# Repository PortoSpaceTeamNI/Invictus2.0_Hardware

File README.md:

Este repositório é usado para gerir as versões dos projetos KiCAD do sistema de Avionics da Porto Space Team.
Está dividido em 2 secções: 
  1. A biblioteca de símbolos, footprints e modelos 3D dos diversos componentes usados no design, cada pasta do símbolo deve apenas incluir os ficheiros de .kicad_sym, .kicad_mod e .step todos juntos apenas dentro de uma única pasta com um nome adequado.
  2. A pasta Boards que contém os diversos ficheiros de schematic (.kicad_sch), pcb (.kicad_pcb) e project (.kicad_pro) de todo o sistema de Avionics.

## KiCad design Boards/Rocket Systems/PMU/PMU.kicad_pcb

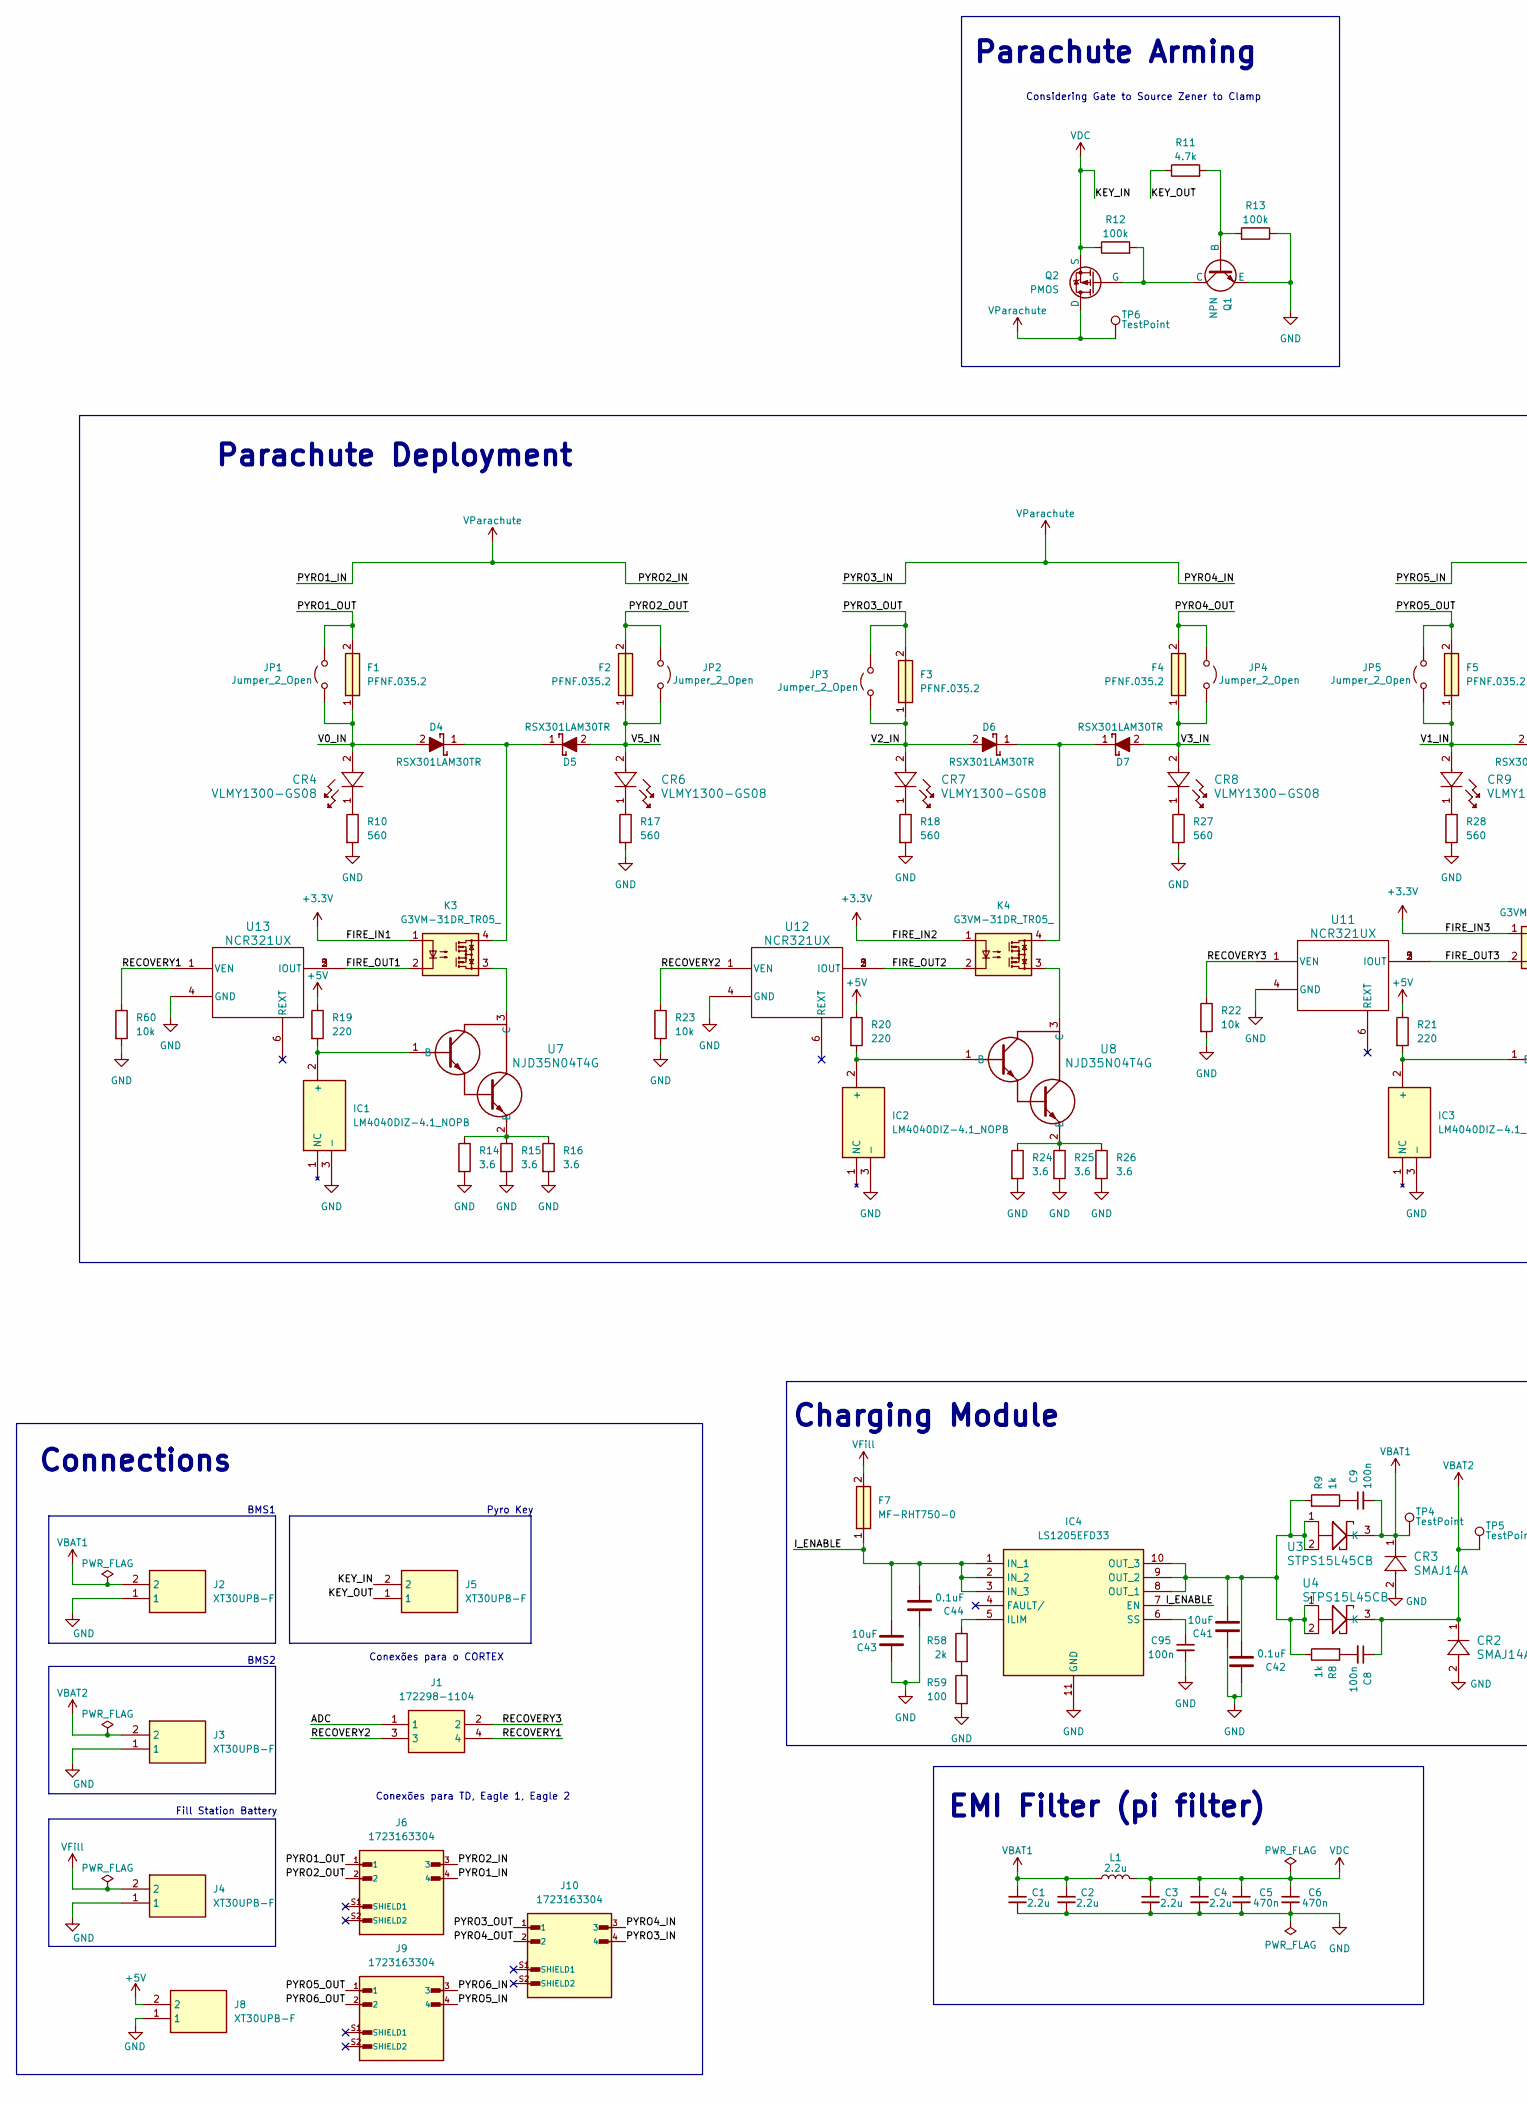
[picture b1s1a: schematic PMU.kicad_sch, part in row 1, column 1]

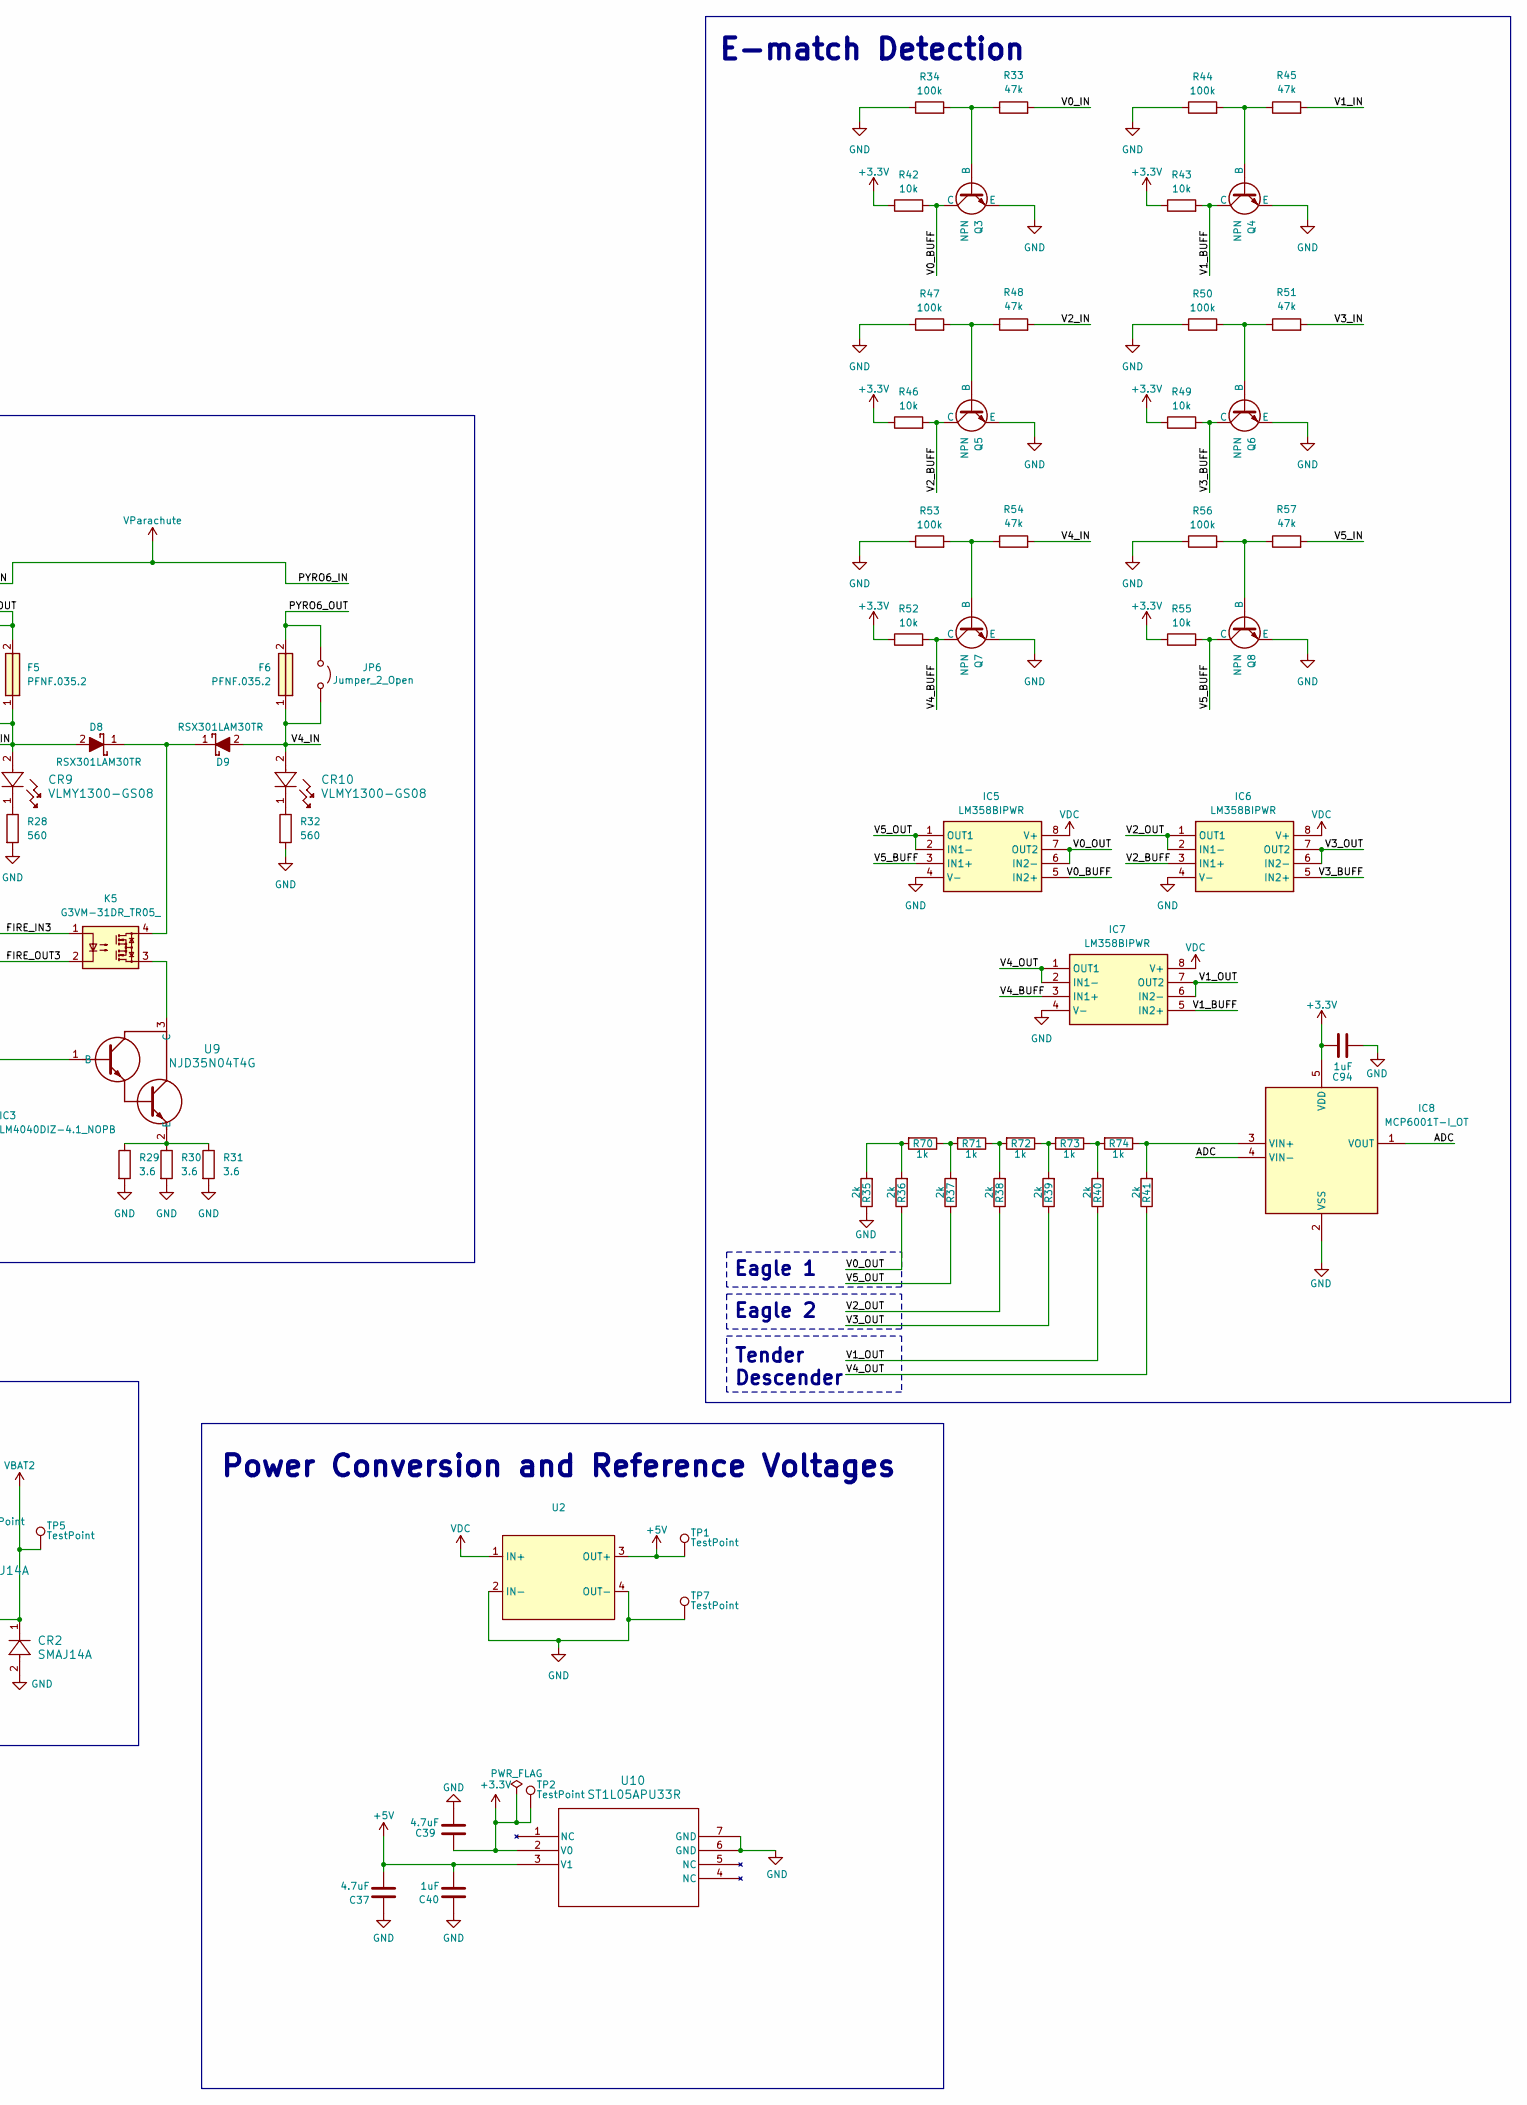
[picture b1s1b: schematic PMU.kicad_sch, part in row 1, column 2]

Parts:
C1, C2, C3, C4: 2.2u; Capacitor_1206
C5, C6: 470n; Capacitor_1206
C8, C9: 100n; Capacitor_0603
C37, C39: 4.7uF; Capacitor_0402
C40, C94: 1uF; Capacitor_0402
C41, C43: 10uF; Capacitor_0402
C42, C44: 0.1uF; Capacitor_0402
C95: 100n; Capacitor_0402
CR2, CR3: SMAJ14A; SMASeries_LTF
CR4, CR6, CR7, CR8, CR9, CR10: VLMY1300-GS08; LEDC1608X100N
D4, D5, D6, D7, D8, D9: RSX301LAM30TR; DIOM5026X220N; Mouser Part Number 755-RSX301L-30DDTE25
F1, F2, F3, F4, F5, F6: PFNF.035.2; FUS1206_24N_SCH; Mouser Part Number 693-PFNF.035.2
F7: MF-RHT750-0; MFRHT7500; Mouser Part Number 693-PFNF.035.2
IC1, IC2, IC3: LM4040DIZ-4.1_NOPB; LM336BLPE325; Mouser Part Number 926-LM4040DIZ41NOPB
IC4: LS1205EFD33; SON50P300X300X80-11N; Mouser Part Number 576-LS1205EFD33
IC5, IC6, IC7: LM358BIPWR; SOP65P640X120-8N; Mouser Part Number 595-LM358BIPWR
IC8: MCP6001T-I_OT; SOT95P270X145-5N; Mouser Part Number 579-MCP6001T-I/OT
J1: 172298-1104; 172298-YY04; Mouser Part Number 538-172298-1104
J2, J3, J4, J5, J8: XT30UPB-F; XT30UPBF; Manufacturer_Part_Number XT30UPB-F
J6, J9, J10: 1723163304; MOLEX_1723163304; PARTREV D
JP1, JP2, JP3, JP4, JP5, JP6: Jumper_2_Open; SolderJumper-2_P1.3mm_Open_RoundedPad1.0x1.5mm
K3, K4, K5: G3VM-31DR_TR05_; G3VM31DRTR05; Mouser Part Number 653-G3VM-31DR(TR05)
L1: 2.2u; SPM10065VT-2R2M-D
Q1, Q3, Q4, Q5, Q6, Q7, Q8: NPN; SOT95P230X110-3N
Q2: PMOS; IPD380P06NMATMA1
R8, R9: 1k; RES_0805
R10, R17, R18, R27, R28, R32: 560; RES_0805
R11: 4.7k; RES_0805
R12, R13: 100k; RES_0805
R14, R15, R16, R24, R25, R26, R29, R30, R31: 3.6; RESC3263X80N
R19, R20, R21: 220; RES_0805
R22, R23, R60: 10k; RES_0402
R33, R45, R48, R51, R54, R57: 47k; RES_0603
R34, R44, R47, R50, R53, R56: 100k; RES_0603
R35, R36, R37, R38, R39, R40, R41, R58: 2k; RES_0603
R42, R43, R46, R49, R52, R55: 10k; RES_0603
R59: 100; RES_0603
R70, R71, R72, R73, R74: 1k; RES_0603
TP1, TP2, TP4, TP5, TP6, TP7: TestPoint; TestPoint_Pad_2.0x2.0mm
U2: DCDC_Module
U3, U4: STPS15L45CB; DPAK_STM
U7, U8, U9: NJD35N04T4G; DPAK-4_6P22X6P73_ONS
U10: ST1L05APU33R; DFN_5APU33R_STM
U11, U12, U13: NCR321UX; TSOP6_SOT457_NEX

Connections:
+3.3V: C39.2, C94.1, IC8.5 (VDD), K3.1, K4.1, K5.1, R42.1, R43.1, R46.1, R49.1, R52.1, R55.1, TP2.1, U10.2 (V0)
+5V: C37.2, C40.2, J8.2, R19.1, R20.1, R21.1, TP1.1, U2.3 (OUT+), U10.3 (V1)
/ADC: IC8.1 (VOUT), IC8.4 (VIN-), J1.1
/FIRE_OUT1: K3.2, U13.2 (IOUT), U13.3 (IOUT), U13.5 (IOUT)
/FIRE_OUT2: K4.2, U12.2 (IOUT), U12.3 (IOUT), U12.5 (IOUT)
/FIRE_OUT3: K5.2, U11.2 (IOUT), U11.3 (IOUT), U11.5 (IOUT)
/I_ENABLE: C43.2, C44.2, F7.1, IC4.1 (IN_1), IC4.2 (IN_2), IC4.3 (IN_3), IC4.7 (EN)
/KEY_OUT: J5.1, R11.1
/PYRO1_OUT: F1.2, J6.1, JP1.2 (B)
/PYRO2_OUT: F2.2, J6.2, JP2.2 (B)
/PYRO3_OUT: F3.2, J10.1, JP3.2 (B)
/PYRO4_OUT: F4.2, J10.2, JP4.2 (B)
/PYRO5_OUT: F5.2, J9.1, JP5.2 (B)
/PYRO6_OUT: F6.2, J9.2, JP6.2 (B)
/RECOVERY1: J1.4, R60.1, U13.1 (VEN)
/RECOVERY2: J1.3, R23.1, U12.1 (VEN)
/RECOVERY3: J1.2, R22.1, U11.1 (VEN)
/V0_BUFF: IC5.5 (IN2+), Q3.1 (C), R42.2
/V0_IN: CR4.2, D4.2 (A), F1.1, JP1.1 (A), R33.2
/V0_OUT: IC5.6 (IN2-), IC5.7 (OUT2), R36.1
/V1_BUFF: IC7.5 (IN2+), Q4.1 (C), R43.2
/V1_IN: CR9.2, D8.2 (A), F5.1, JP5.1 (A), R45.2
/V1_OUT: IC7.6 (IN2-), IC7.7 (OUT2), R40.1
/V2_BUFF: IC6.3 (IN1+), Q5.1 (C), R46.2
/V2_IN: CR7.2, D6.2 (A), F3.1, JP3.1 (A), R48.2
/V2_OUT: IC6.1 (OUT1), IC6.2 (IN1-), R38.1
/V3_BUFF: IC6.5 (IN2+), Q6.1 (C), R49.2
/V3_IN: CR8.2, D7.2 (A), F4.1, JP4.1 (A), R51.2
/V3_OUT: IC6.6 (IN2-), IC6.7 (OUT2), R39.1
/V4_BUFF: IC7.3 (IN1+), Q7.1 (C), R52.2
/V4_IN: CR10.2, D9.2 (A), F6.1, JP6.1 (A), R54.2
/V4_OUT: IC7.1 (OUT1), IC7.2 (IN1-), R41.1
/V5_BUFF: IC5.3 (IN1+), Q8.1 (C), R55.2
/V5_IN: CR6.2, D5.2 (A), F2.1, JP2.1 (A), R57.2
/V5_OUT: IC5.1 (OUT1), IC5.2 (IN1-), R37.1
GND: C1.2, C2.2, C3.2, C4.2, C5.2, C6.2, C37.1, C39.1, C40.1, C41.1, C42.1, C43.1, C44.1, C94.2, C95.2, CR2.2, CR3.2, IC1.3 (-), IC2.3 (-), IC3.3 (-), IC4.11 (GND), IC5.4 (V-), IC6.4 (V-), IC7.4 (V-), IC8.2 (VSS), J2.1, J3.1, J4.1, J8.1, Q1.3 (E), Q3.3 (E), Q4.3 (E), Q5.3 (E), Q6.3 (E), Q7.3 (E), Q8.3 (E), R10.2, R13.1, R14.2, R15.2, R16.2, R17.2, R18.2, R22.2, R23.2, R24.2, R25.2, R26.2, R27.2, R28.2, R29.2, R30.2, R31.2, R32.2, R34.1, R35.1, R44.1, R47.1, R50.1, R53.1, R56.1, R59.2, R60.2, TP7.1, U2.2 (IN-), U2.4 (OUT-), U10.6 (GND), U10.7 (GND), U11.4 (GND), U12.4 (GND), U13.4 (GND)
unnamed: C8.2, R8.2
unnamed: C9.1, R9.1
unnamed: CR4.1, R10.1
unnamed: CR6.1, R17.1
unnamed: CR7.1, R18.1
unnamed: CR8.1, R27.1
unnamed: CR9.1, R28.1
unnamed: CR10.1, R32.1
unnamed: D4.1 (K), D5.1 (K), K3.4
unnamed: D6.1 (K), D7.1 (K), K4.4
unnamed: D8.1 (K), D9.1 (K), K5.4
unnamed: IC1.2 (+), R19.2, U7.1 (B)
unnamed: IC2.2 (+), R20.2, U8.1 (B)
unnamed: IC3.2 (+), R21.2, U9.1 (B)
unnamed: IC4.5 (ILIM), R58.1
unnamed: C41.2, C42.2, IC4.8 (OUT_1), IC4.9 (OUT_2), IC4.10 (OUT_3), R8.1, R9.2, U3.1, U3.2, U4.1, U4.2
unnamed: C95.1, IC4.6 (SS)
unnamed: IC8.3 (VIN+), R41.2, R74.1
unnamed: Q1.2 (B), R11.2, R13.2
unnamed: Q1.1 (C), Q2.2 (G), R12.2
unnamed: Q3.2 (B), R33.1, R34.2
unnamed: Q4.2 (B), R44.2, R45.1
unnamed: Q5.2 (B), R47.2, R48.1
unnamed: Q6.2 (B), R50.2, R51.1
unnamed: Q7.2 (B), R53.2, R54.1
unnamed: Q8.2 (B), R56.2, R57.1
unnamed: R35.2, R36.2, R70.2
unnamed: R37.2, R70.1, R71.2
unnamed: R38.2, R71.1, R72.2
unnamed: R39.2, R72.1, R73.2
unnamed: R40.2, R73.1, R74.2
unnamed: R58.2, R59.1
unnamed: K3.3, U7.3 (C)
unnamed: R14.1, R15.1, R16.1, U7.2 (E)
unnamed: K4.3, U8.3 (C)
unnamed: R24.1, R25.1, R26.1, U8.2 (E)
unnamed: K5.3, U9.3 (C)
unnamed: R29.1, R30.1, R31.1, U9.2 (E)
VBAT1: C1.1, C2.1, C9.2, CR3.1, J2.2, L1.1, TP4.1, U3.3 (K)
VBAT2: C8.1, CR2.1, J3.2, TP5.1, U4.3 (K)
VDC: C3.1, C4.1, C5.1, C6.1, IC5.8 (V+), IC6.8 (V+), IC7.8 (V+), J5.2, L1.2, Q2.3 (S), R12.1, U2.1 (IN+)
VFill: F7.2, J4.2
VParachute: J6.3, J6.4, J9.3, J9.4, J10.3, J10.4, Q2.1 (D), TP6.1

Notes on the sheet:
Pyro Key
BMS1
Conexões para o CORTEX
Parachute Arming
E-match Detection
Connections
Power Conversion and Reference Voltages
Considering Gate to Source Zener to Clamp
BMS2
Charging Module
Fill Station Battery
Conexões para TD, Eagle 1, Eagle 2
Parachute Deployment
Eagle 2
EMI Filter (pi filter)
Eagle 1
Tender Descender

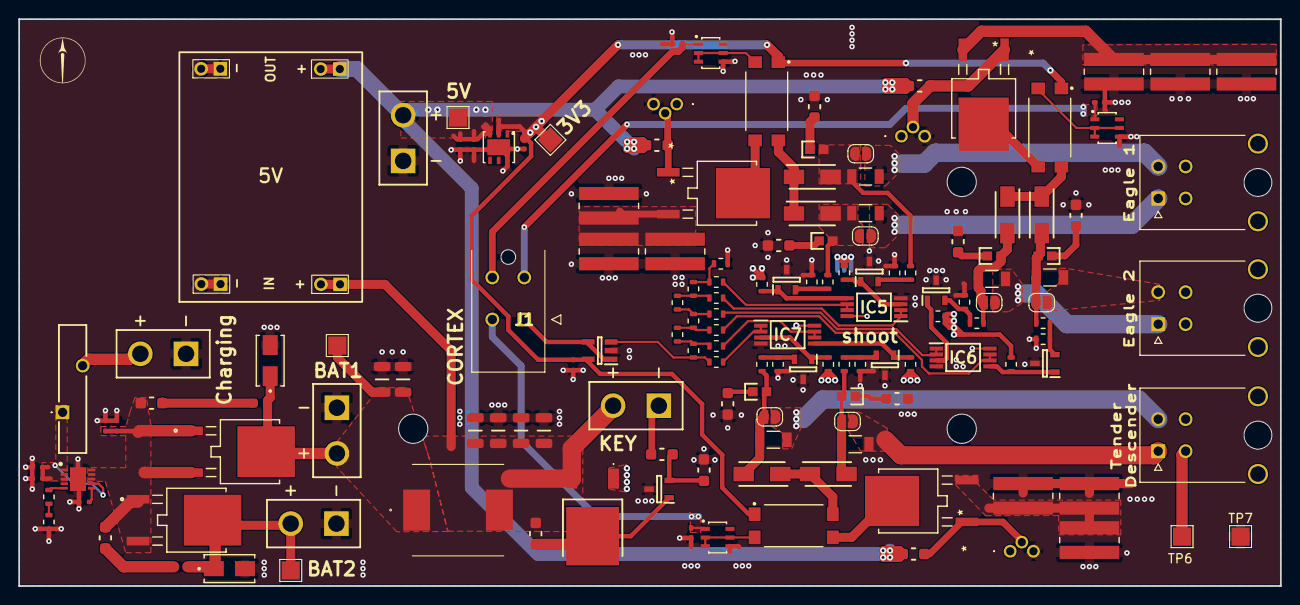
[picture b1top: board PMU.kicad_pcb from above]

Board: 4 copper layers, 138.0 x 62.0 mm, 150 parts (0 on the bottom side), 79 nets.

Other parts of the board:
H1, H2, H3: MountingHole; MountingHole_3.2mm_M3_ISO7380

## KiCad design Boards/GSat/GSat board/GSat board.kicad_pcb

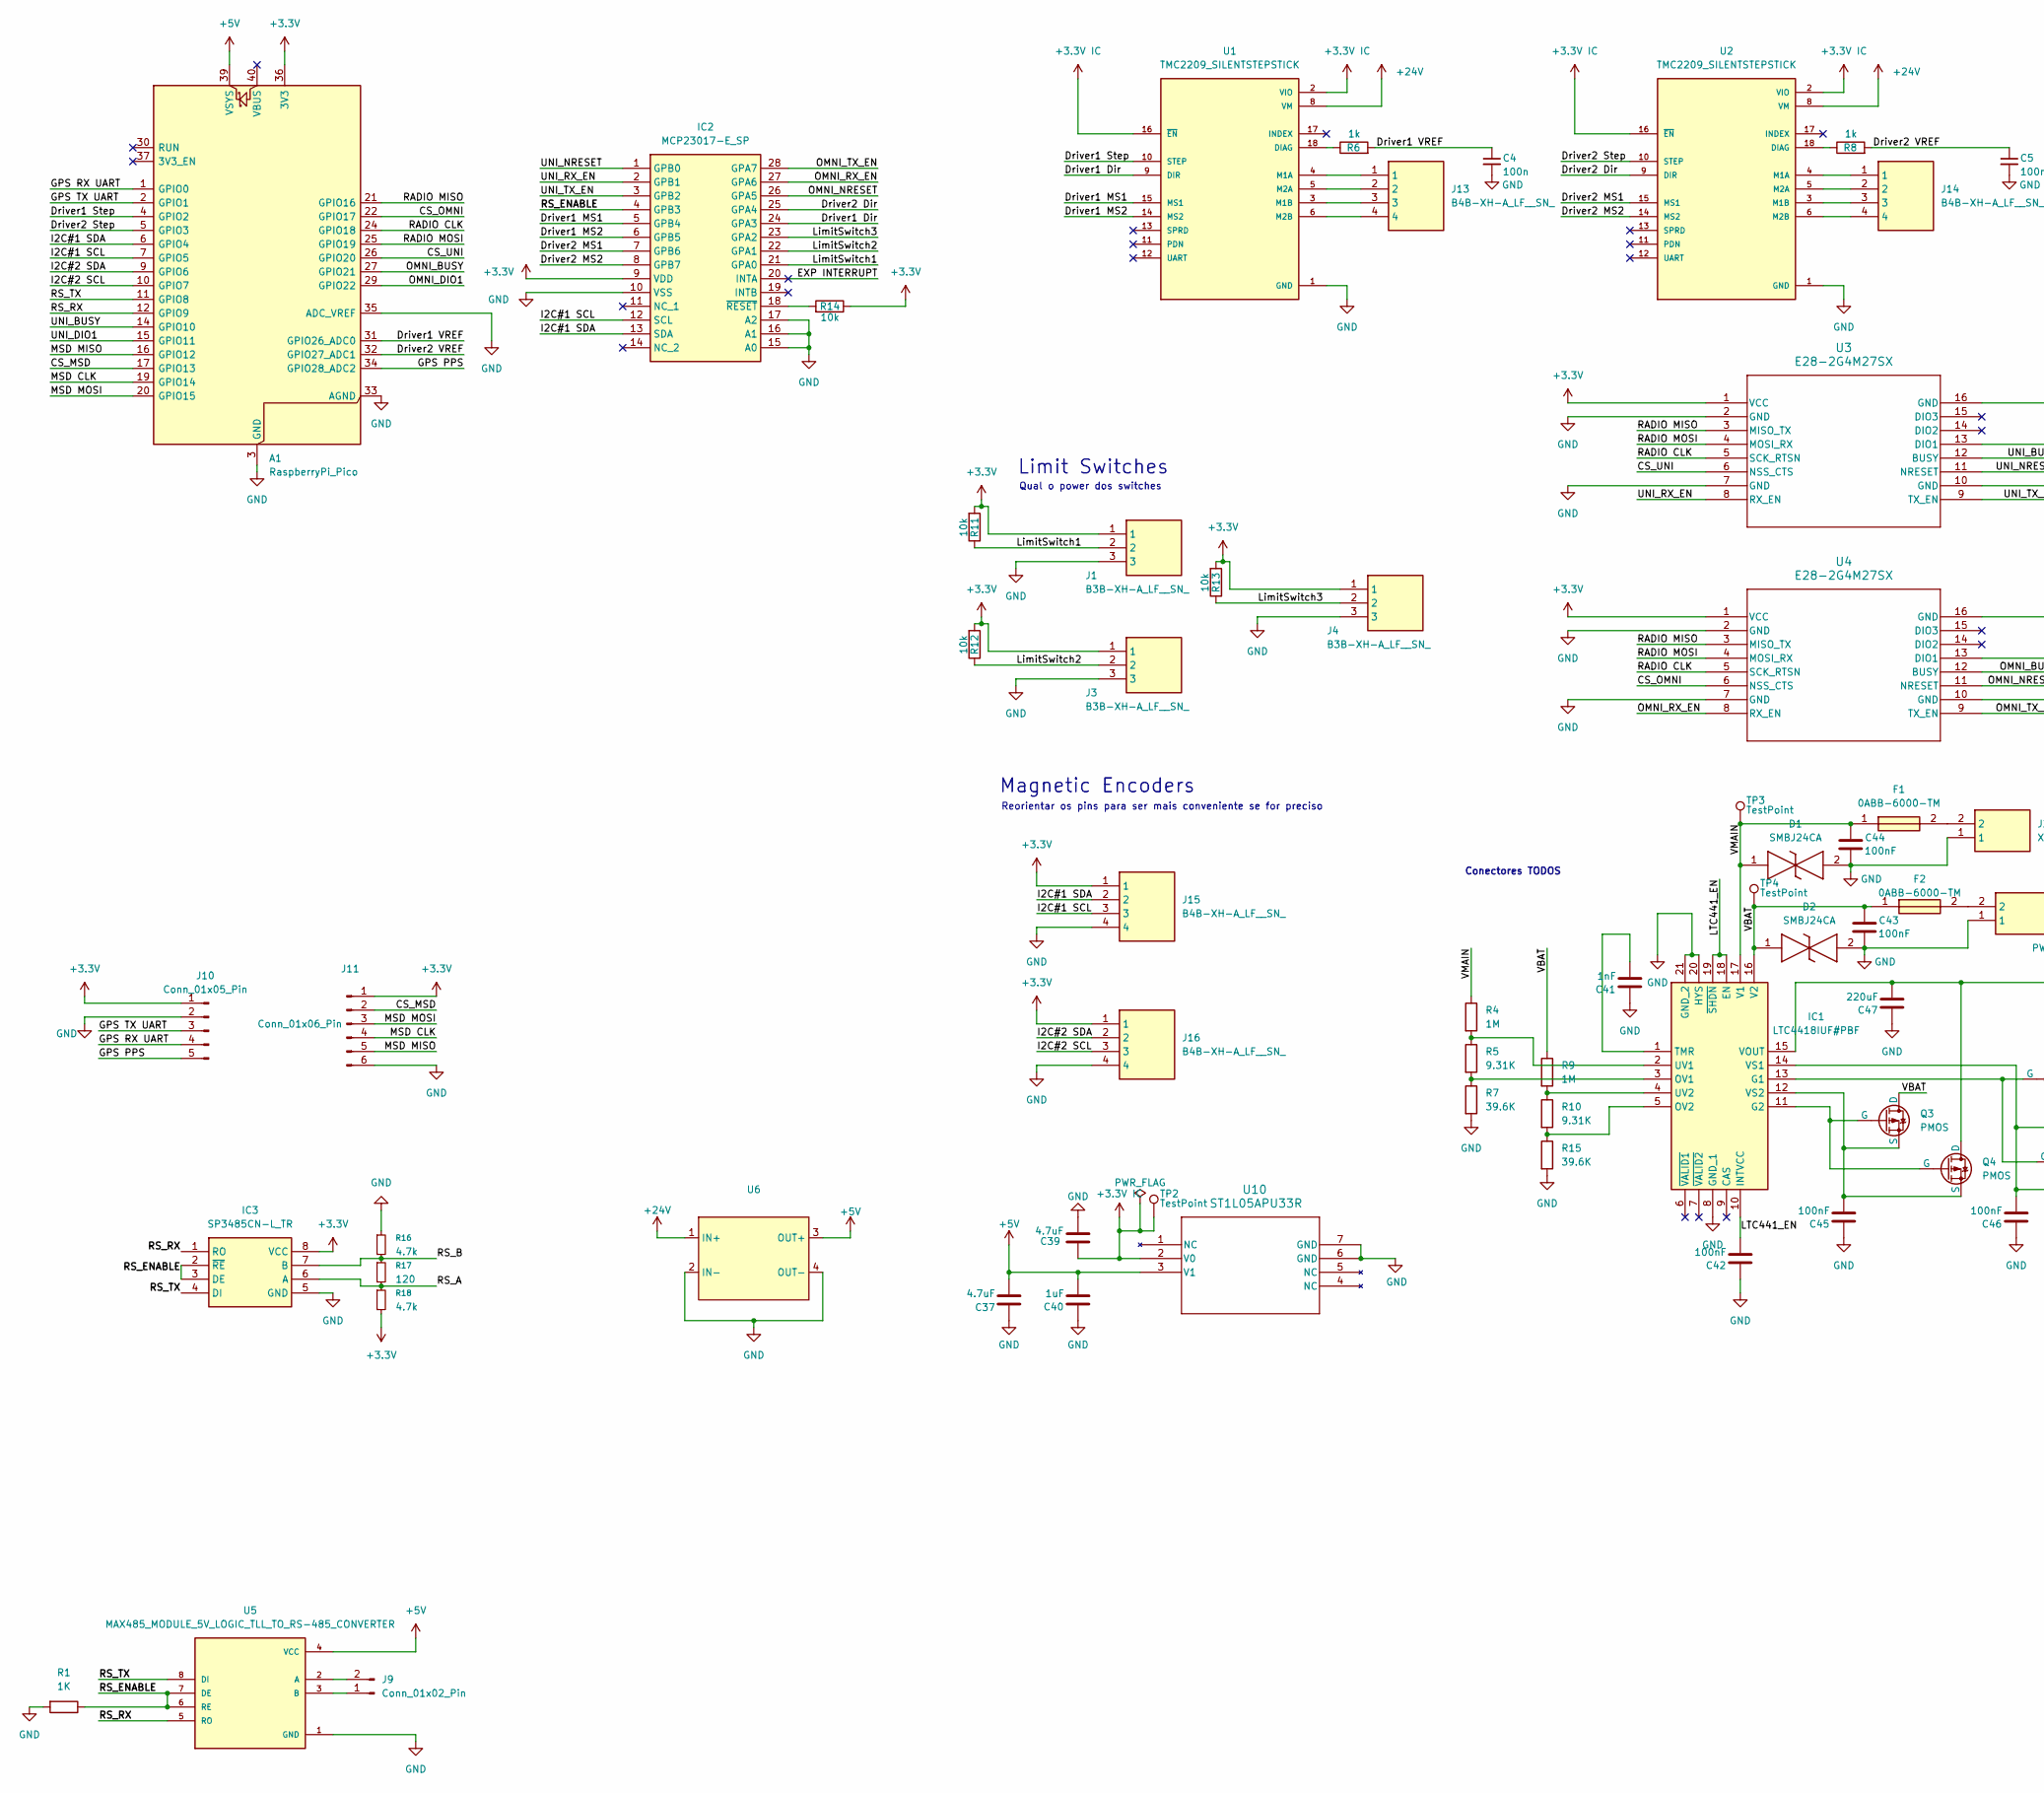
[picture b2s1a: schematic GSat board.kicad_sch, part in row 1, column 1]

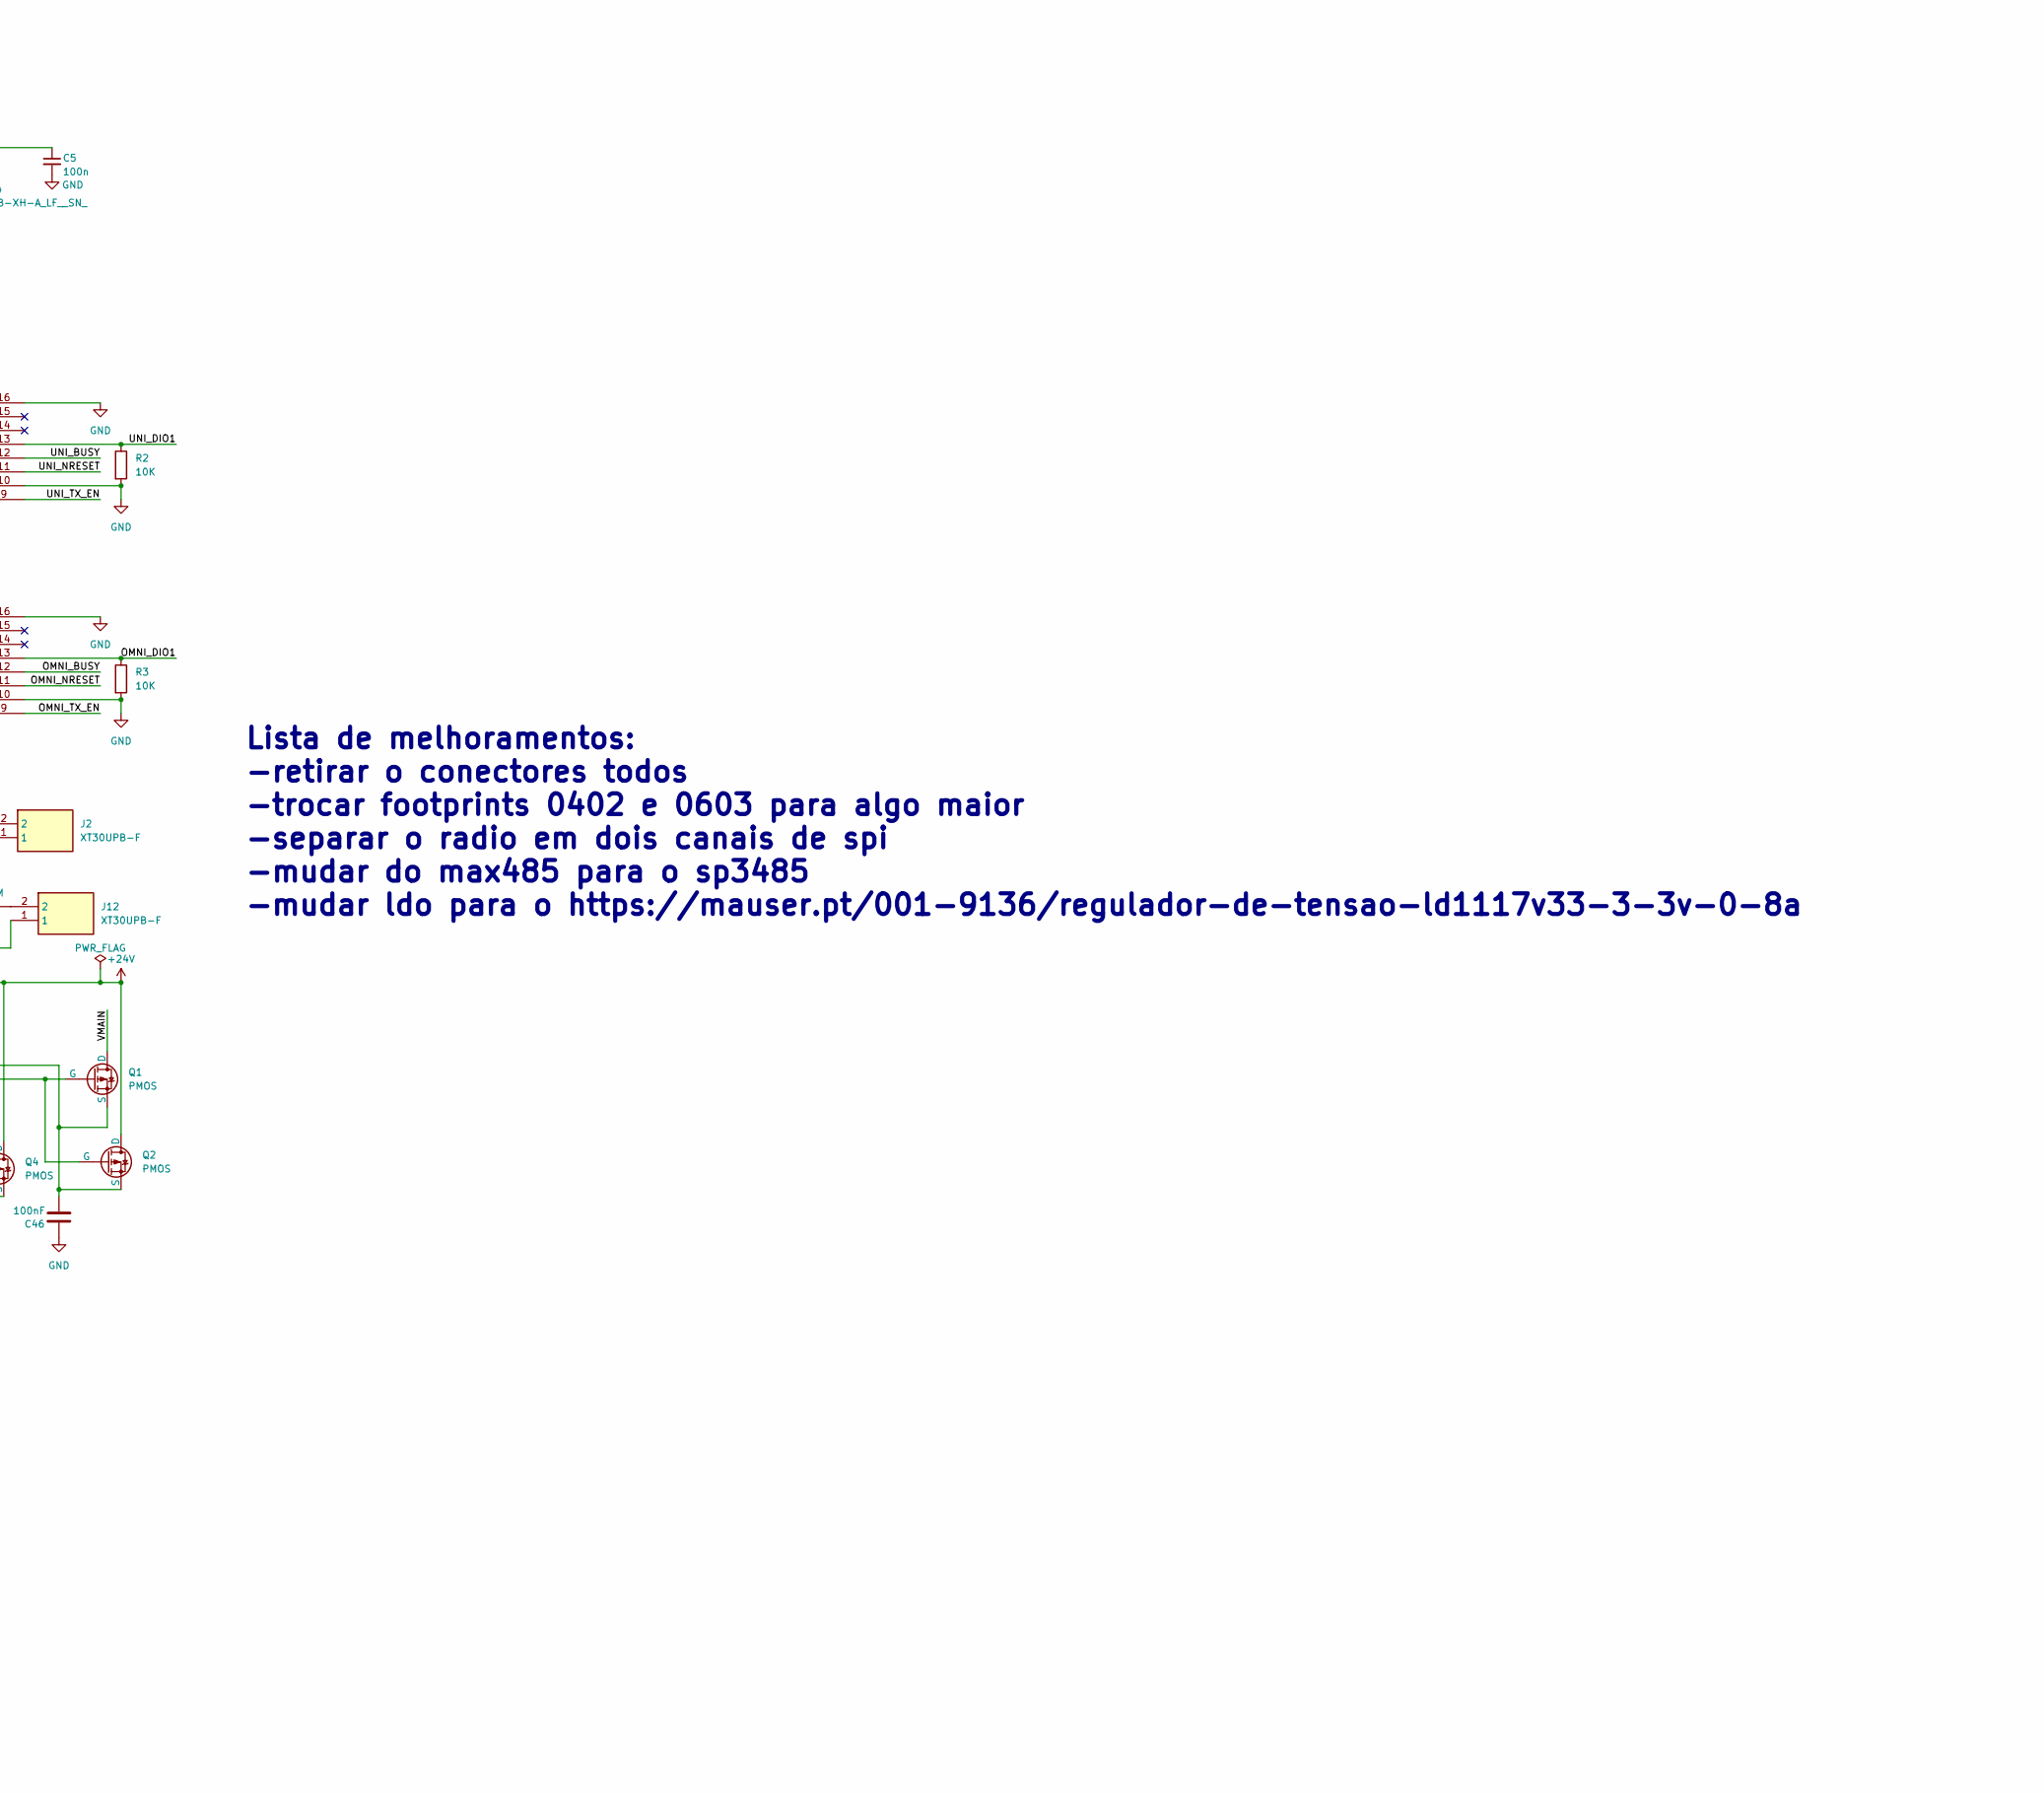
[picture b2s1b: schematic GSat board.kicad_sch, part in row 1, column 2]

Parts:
A1: RaspberryPi_Pico; RaspberryPi_Pico_Common_Unspecified
C4, C5: 100n; Capacitor_0402
C37, C39: 4.7uF; Capacitor_0402
C40: 1uF; Capacitor_0402
C41: 1nF; Capacitor_0402
C42, C43, C44, C45, C46: 100nF; Capacitor_0402
C47: 220uF; Capacitor_0402
D1, D2: SMBJ24CA; DIOM5436X244N; Mouser Part Number 576-SMBJ24CA
F1, F2: 0ABB-6000-TM; 0ABB6000TM; Mouser Part Number 530-0ABB-6000-TM
IC1: LTC4418IUF#PBF; QFN50P400X400X80-21N-D; Mouser Part Number 584-LTC4418IUFPBF
IC2: MCP23017-E_SP; DIP794W56P254L3486H508Q28N; Mouser Part Number 579-MCP23017-E/SP
IC3: SP3485CN-L_TR; SOIC127P600X175-8N; Mouser Part Number 701-SP3485CN-L/TR
J1, J3, J4: B3B-XH-A_LF__SN_; B3BXHALFSN; Mouser Part Number 306-B3BXHALFSNP
J2, J12: XT30UPB-F; XT30UPBF; Manufacturer_Part_Number XT30UPB-F
J9: Conn_01x02_Pin
J10: Conn_01x05_Pin; PinSocket_1x05_P2.54mm_Vertical
J11: Conn_01x06_Pin; PinSocket_1x06_P2.54mm_Vertical
J13, J14, J15, J16: B4B-XH-A_LF__SN_; B4BXHALFSN; Mouser Part Number 306-B4BXHALFSN
Q1, Q2, Q3, Q4: PMOS; TO-252-3_TabPin2
R1: 1K; R_0603_1608Metric_Pad0.98x0.95mm_HandSolder
R2, R3: 10K; R_0603_1608Metric_Pad0.98x0.95mm_HandSolder
R4, R9: 1M; R_0603_1608Metric_Pad0.98x0.95mm_HandSolder
R5, R10: 9.31K; R_0603_1608Metric_Pad0.98x0.95mm_HandSolder
R6, R8: 1k; RES_0402
R7, R15: 39.6K; R_0603_1608Metric_Pad0.98x0.95mm_HandSolder
R11, R12, R13, R14: 10k; RES_0402
R16, R18: 4.7k; R_0603_1608Metric_Pad0.98x0.95mm_HandSolder
R17: 120; R_0603_1608Metric_Pad0.98x0.95mm_HandSolder
TP2, TP3, TP4: TestPoint; TestPoint_Pad_2.0x2.0mm
U1, U2: TMC2209_SILENTSTEPSTICK; MODULE_TMC2209_SILENTSTEPSTICK; PARTREV 1.20
U3, U4: E28-2G4M27SX; Radio_Module_PST
U5: MAX485_MODULE_5V_LOGIC_TLL_TO_RS-485_CONVERTER; MODULE_MAX485_MODULE_5V_LOGIC_TLL_TO_RS-485_CONVERTER; PARTREV 1r0
U6: DCDC_Module
U10: ST1L05APU33R; DFN_5APU33R_STM

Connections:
+3.3V: A1.36 (3V3), IC2.9 (VDD), IC3.8 (VCC), J1.1, J3.1, J4.1, J10.1, J11.1, J15.1, J16.1, R11.2, R12.2, R13.2, R14.1, R18.2, U3.1 (VCC), U4.1 (VCC)
+3.3V IC: C39.2, TP2.1 (1_1), U1.2 (VIO), U1.16 (~EN), U2.2 (VIO), U2.16 (~EN), U10.2 (V0)
+5V: A1.39 (VSYS), C37.2, C40.2, U5.4 (VCC), U6.3 (OUT+), U10.3 (V1)
+24V: C47.2, IC1.15 (VOUT), Q2.2 (D), Q4.2 (D), U1.8 (VM), U2.8 (VM), U6.1 (IN+)
/CS_MSD: A1.17 (GPIO13), J11.2
/CS_OMNI: A1.22 (GPIO17), U4.6 (NSS_CTS)
/CS_UNI: A1.26 (GPIO20), U3.6 (NSS_CTS)
/Driver1 Dir: IC2.24 (GPA3), U1.9 (DIR)
/Driver1 MS1: IC2.5 (GPB4), U1.15 (MS1)
/Driver1 MS2: IC2.6 (GPB5), U1.14 (MS2)
/Driver1 Step: A1.4 (GPIO2), U1.10 (STEP)
/Driver1 VREF: A1.31 (GPIO26_ADC0), C4.1, R6.2
/Driver2 Dir: IC2.25 (GPA4), U2.9 (DIR)
/Driver2 MS1: IC2.7 (GPB6), U2.15 (MS1)
/Driver2 MS2: IC2.8 (GPB7), U2.14 (MS2)
/Driver2 Step: A1.5 (GPIO3), U2.10 (STEP)
/Driver2 VREF: A1.32 (GPIO27_ADC1), C5.1, R8.2
/EXP INTERRUPT: IC2.20 (INTA)
/GPS PPS: A1.34 (GPIO28_ADC2), J10.5
/GPS RX UART: A1.1 (GPIO0), J10.4
/GPS TX UART: A1.2 (GPIO1), J10.3
/I2C#1 SCL: A1.7 (GPIO5), IC2.12 (SCL), J15.3
/I2C#1 SDA: A1.6 (GPIO4), IC2.13 (SDA), J15.2
/I2C#2 SCL: A1.10 (GPIO7), J16.3
/I2C#2 SDA: A1.9 (GPIO6), J16.2
/LTC441_EN: C42.2, IC1.10 (INTVCC), IC1.18 (EN), IC1.19 (~SHDN)
/LimitSwitch1: IC2.21 (GPA0), J1.2, R11.1
/LimitSwitch2: IC2.22 (GPA1), J3.2, R12.1
/LimitSwitch3: IC2.23 (GPA2), J4.2, R13.1
/MSD CLK: A1.19 (GPIO14), J11.4
/MSD MISO: A1.16 (GPIO12), J11.5
/MSD MOSI: A1.20 (GPIO15), J11.3
/OMNI_BUSY: A1.27 (GPIO21), U4.12 (BUSY)
/OMNI_DIO1: A1.29 (GPIO22), R3.1, U4.13 (DIO1)
/OMNI_NRESET: IC2.26 (GPA5), U4.11 (NRESET)
/OMNI_RX_EN: IC2.27 (GPA6), U4.8 (RX_EN)
/OMNI_TX_EN: IC2.28 (GPA7), U4.9 (TX_EN)
/RADIO CLK: A1.24 (GPIO18), U3.5 (SCK_RTSN), U4.5 (SCK_RTSN)
/RADIO MISO: A1.21 (GPIO16), U3.3 (MISO_TX), U4.3 (MISO_TX)
/RADIO MOSI: A1.25 (GPIO19), U3.4 (MOSI_RX), U4.4 (MOSI_RX)
/RS_A: IC3.6 (A), R17.2, R18.1
/RS_B: IC3.7 (B), R16.2, R17.1
/RS_ENABLE: IC2.4 (GPB3), IC3.2 (~RE), IC3.3 (DE), R1.1, U5.6 (RE), U5.7 (DE)
/RS_RX: A1.12 (GPIO9), IC3.1 (RO), U5.5 (RO)
/RS_TX: A1.11 (GPIO8), IC3.4 (DI), U5.8 (DI)
/UNI_BUSY: A1.14 (GPIO10), U3.12 (BUSY)
/UNI_DIO1: A1.15 (GPIO11), R2.1, U3.13 (DIO1)
/UNI_NRESET: IC2.1 (GPB0), U3.11 (NRESET)
/UNI_RX_EN: IC2.2 (GPB1), U3.8 (RX_EN)
/UNI_TX_EN: IC2.3 (GPB2), U3.9 (TX_EN)
/VBAT: C43.1, D2.1, F2.1, IC1.16 (V2), Q3.2 (D), R9.1, TP4.1 (1_1)
/VMAIN: C44.1, D1.1, F1.1, IC1.17 (V1), Q1.2 (D), R4.1, TP3.1 (1_1)
GND: A1.3 (GND), A1.8 (GND), A1.13 (GND), A1.18 (GND), A1.23 (GND), A1.28 (GND), A1.33 (AGND), A1.35 (ADC_VREF), A1.38 (GND), C4.2, C5.2, C37.1, C39.1, C40.1, C41.1, C42.1, C43.2, C44.2, C45.1, C46.1, C47.1, D1.2, D2.2, IC1.8 (GND_1), IC1.20 (HYS), IC1.21 (GND_2), IC2.10 (VSS), IC2.15 (A0), IC2.16 (A1), IC2.17 (A2), IC3.5 (GND), J1.3, J2.1, J3.3, J4.3, J10.2, J11.6, J12.1, J15.4, J16.4, R1.2, R2.2, R3.2, R7.2, R15.2, R16.1, U1.1 (GND), U1.7 (GND), U2.1 (GND), U2.7 (GND), U3.2 (GND), U3.7 (GND), U3.10 (GND), U3.16 (GND), U4.2 (GND), U4.7 (GND), U4.10 (GND), U4.16 (GND), U5.1 (GND), U6.2 (IN-), U6.4 (OUT-), U10.6 (GND), U10.7 (GND)
unnamed: F1.2, J2.2
unnamed: F2.2, J12.2
unnamed: IC1.13 (G1), Q1.1 (G), Q2.1 (G)
unnamed: IC1.11 (G2), Q3.1 (G), Q4.1 (G)
unnamed: IC1.3 (OV1), R5.2, R7.1
unnamed: IC1.5 (OV2), R10.2, R15.1
unnamed: C41.2, IC1.1 (TMR)
unnamed: IC1.2 (UV1), R4.2, R5.1
unnamed: IC1.4 (UV2), R9.2, R10.1
unnamed: C46.2, IC1.14 (VS1), Q1.3 (S), Q2.3 (S)
unnamed: C45.2, IC1.12 (VS2), Q3.3 (S), Q4.3 (S)
unnamed: IC2.18 (~RESET), R14.2
unnamed: J9.1, U5.3 (B)
unnamed: J9.2, U5.2 (A)
unnamed: R6.1, U1.18 (DIAG)
unnamed: J13.1, U1.4 (M1A)
unnamed: J13.3, U1.3 (M1B)
unnamed: J13.2, U1.5 (M2A)
unnamed: J13.4, U1.6 (M2B)
unnamed: R8.1, U2.18 (DIAG)
unnamed: J14.1, U2.4 (M1A)
unnamed: J14.3, U2.3 (M1B)
unnamed: J14.2, U2.5 (M2A)
unnamed: J14.4, U2.6 (M2B)

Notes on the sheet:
Lista de melhoramentos: -retirar o conectores todos -trocar footprints 0402 e 0603 para algo maior -separar o radio em dois canais de spi -mudar do max485 para o sp3485 -mudar ldo para o https://mauser.pt/001-9136/regulador-de-tensao-ld1117v33-3-3v-0-8a
Reorientar os pins para ser mais conveniente se for preciso
Conectores TODOS
Qual o power dos switches
Magnetic Encoders
Limit Switches
